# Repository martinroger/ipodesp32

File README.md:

# iPodESP32 : an iPod emulator for 2nd gen Minis

## CAVEAT
> [!WARNING]
> At the time of this commit, it has become apparent that the all CP2102 chips are not born equal. The hack consisting of spoofing a PL2303HX by overwriting the PID and VID on a CP2102 **only works on older versions**. I haven't yet managed to get it to work on CP2102N or CP2102-GM transceivers. Additionally, I haven't managed to get this hack to work on CP2104 or FTDI232R transceivers. For the time being, I would recommend holding off from ordering boards based on the designs in PCB unless you are certain you can source pre-2018 CP2102 chips.
> Work is happening on finding a solution, as the PL2303TA that would be the ideal candidate is hard to find in stock too.
> 
> **I may have found a practical solution by getting an ESP32S3 to spoof being a PL2303HX. Release v1.0.0 will introduce that solution !**

## Summary (TL;DR)

Second generation Minis (R56, R57, R58...) did not come with Bluetooth music streaming unless the Visual Boost or Mini Connected navigation option was selected (which wasn't hugely popular). 
Some of the later Minis (usually called LCI, or facelift Mini) started shipping with iPod support in the form of an USB receptacle, a 3.5mm AUX input and a special "Y-Cable". 

This repository is an attempt at bridging that gap with an ESP32 and a bag of tricks to provide **BT music streaming, retaining track data on the display and radio/steering wheel playback controls.**

## What is needed

Aside from a [Mini with a compatible radio head unit](https://github.com/martinroger/ipodesp32/wiki/How-to-identify-compatible-Minis) : 

- For the [full-DIY build](https://github.com/martinroger/ipodesp32/wiki/DIY-DAC%E2%80%90based-solution-(UDA1334A)) :
  - An ESP32 (not S3!) that has Bluetooth Classic or EDR support
  - A DAC (UDA1334 or PCM5102) breakout board
  - A CP2102 ~~or CP2104~~ breakout board with exposed DCD pin (no CP2102N or CP2102GM)
  - Jumper wires
  - Possibly some smaller hardware (resistors, capacitors) and a soldering iron

- For the Sandwich Carrier Board build, [follow this article](https://github.com/martinroger/ipodesp32/wiki/Sandwich-Carrier-Board-build)
- For the ESP32 AudioKit Top Hat build, [follow this other article](https://github.com/martinroger/ipodesp32/wiki/AudioKit-and-Haut%E2%80%90de%E2%80%90Forme-board)
- For the fancy ones out there wanting a small ESP32 A1S Mini, [it's here](https://github.com/martinroger/ipodesp32/wiki/ESP32%E2%80%90A1S%E2%80%90Mini-build)
- For the fancy but alternative-minded ones who also want an All-In-One, [it's there](https://github.com/martinroger/ipodesp32/wiki/ESP32%E2%80%90AiO-build)

## Alternative solutions

Over the year, some companies (mostly in China) have developped similar devices, such as the ones sold by **[Bovee](https://a.co/d/5lkZTkV)** or **[Gitank](https://thegitank.com/products/gitank-bluetooth-5-0-aptx-hd-adapter-with-y-cable-for-bmw-and-mini-cooper-usb-aux-ipod-iphone-music-interface-300b)**. The general principle is the same : a BT speaker is running an A2DP profile, while sufficient iPod-like communication is performed with the Mini to make it think there is an actual iPod connected.

I have had a very mixed bag of results with those, and it appeared to be even worse when using an Android phone, as the Playback/Synchronisation/Metadata seemed to be mostly reserved to iPhone users. Playback controls were also hit-and-miss.

## The iPodESP32 solution

Beyond the lame name, the solution proposed here does the following :

- Emulates an iPod Classic 5 - the U2 edition to be precise
- Passes song metadata from the phone/tablet (**Android or iOs**... or even others ?) regardless of what is playing the songs (Spotify remains the most tested to this date)
- Enables direct playback control from the radio interface, including steering wheel controls if present
- Auto-reconnects on ignition on, auto-pauses on ignition off
- Auto-pause and passes to whichever handsfree solution is present in case of phone call
- Provides many different interfaces for debug logging... because surely I didn't catch all them bugs
- Does not require any permanent modification of the car

## External (essential) libraries used

Respect where is due to the underlying libraries needed for this to work : 
- [AudioTools](https://github.com/pschatzmann/arduino-audio-tools)
- [ESP32-A2DP library](https://github.com/pschatzmann/ESP32-A2DP)
- [Arduino Audio Driver](https://github.com/pschatzmann/arduino-audio-driver)

## How to use it, and some tips

Although it should be pretty straightforward at this stage, to use this, you need to connect the USB with the modified VID/PID to the USB receptacle of the car, and the audio jack to the AUX input (with a male-male stereo cable, for example).

In its default configuration, the controller will wait for an established BT connection to a phone before it starts signalling to the vehicle that it is available. This is only necessary the first time a phone is connected to it, in other cases the controller will try to auto-reconnect.

Once the controller has established connection with the phone, it starts the handshake process with the head unit, and if all is good the Aux and USB options in the "Mode" source selector of the head unit are replaced by an "iPod" option. This normally takes a few seconds if the controller was just connected, so re-check after 10s if the iPod option is not available.
If it still doesn't come up, in some occasions it is necessary to disconnect the USB cable, wait 5-10 seconds and reconnect it and wait for the BT pairing to go through (check your phone!).

The Mini will try to automatically start playback once the iPod option is selected. Depending on your phone configuration, it may automatically open your favourite music player and start playing. In some cases it might be necessary to manually open a music player for things to get started. At this stage the display should update with the track info.

When you leave the car, the USB gets shut down after about 2 minutes (no risks of draining the battery) and normally the Mini negotiates a playback pause as the ignition is turned off...

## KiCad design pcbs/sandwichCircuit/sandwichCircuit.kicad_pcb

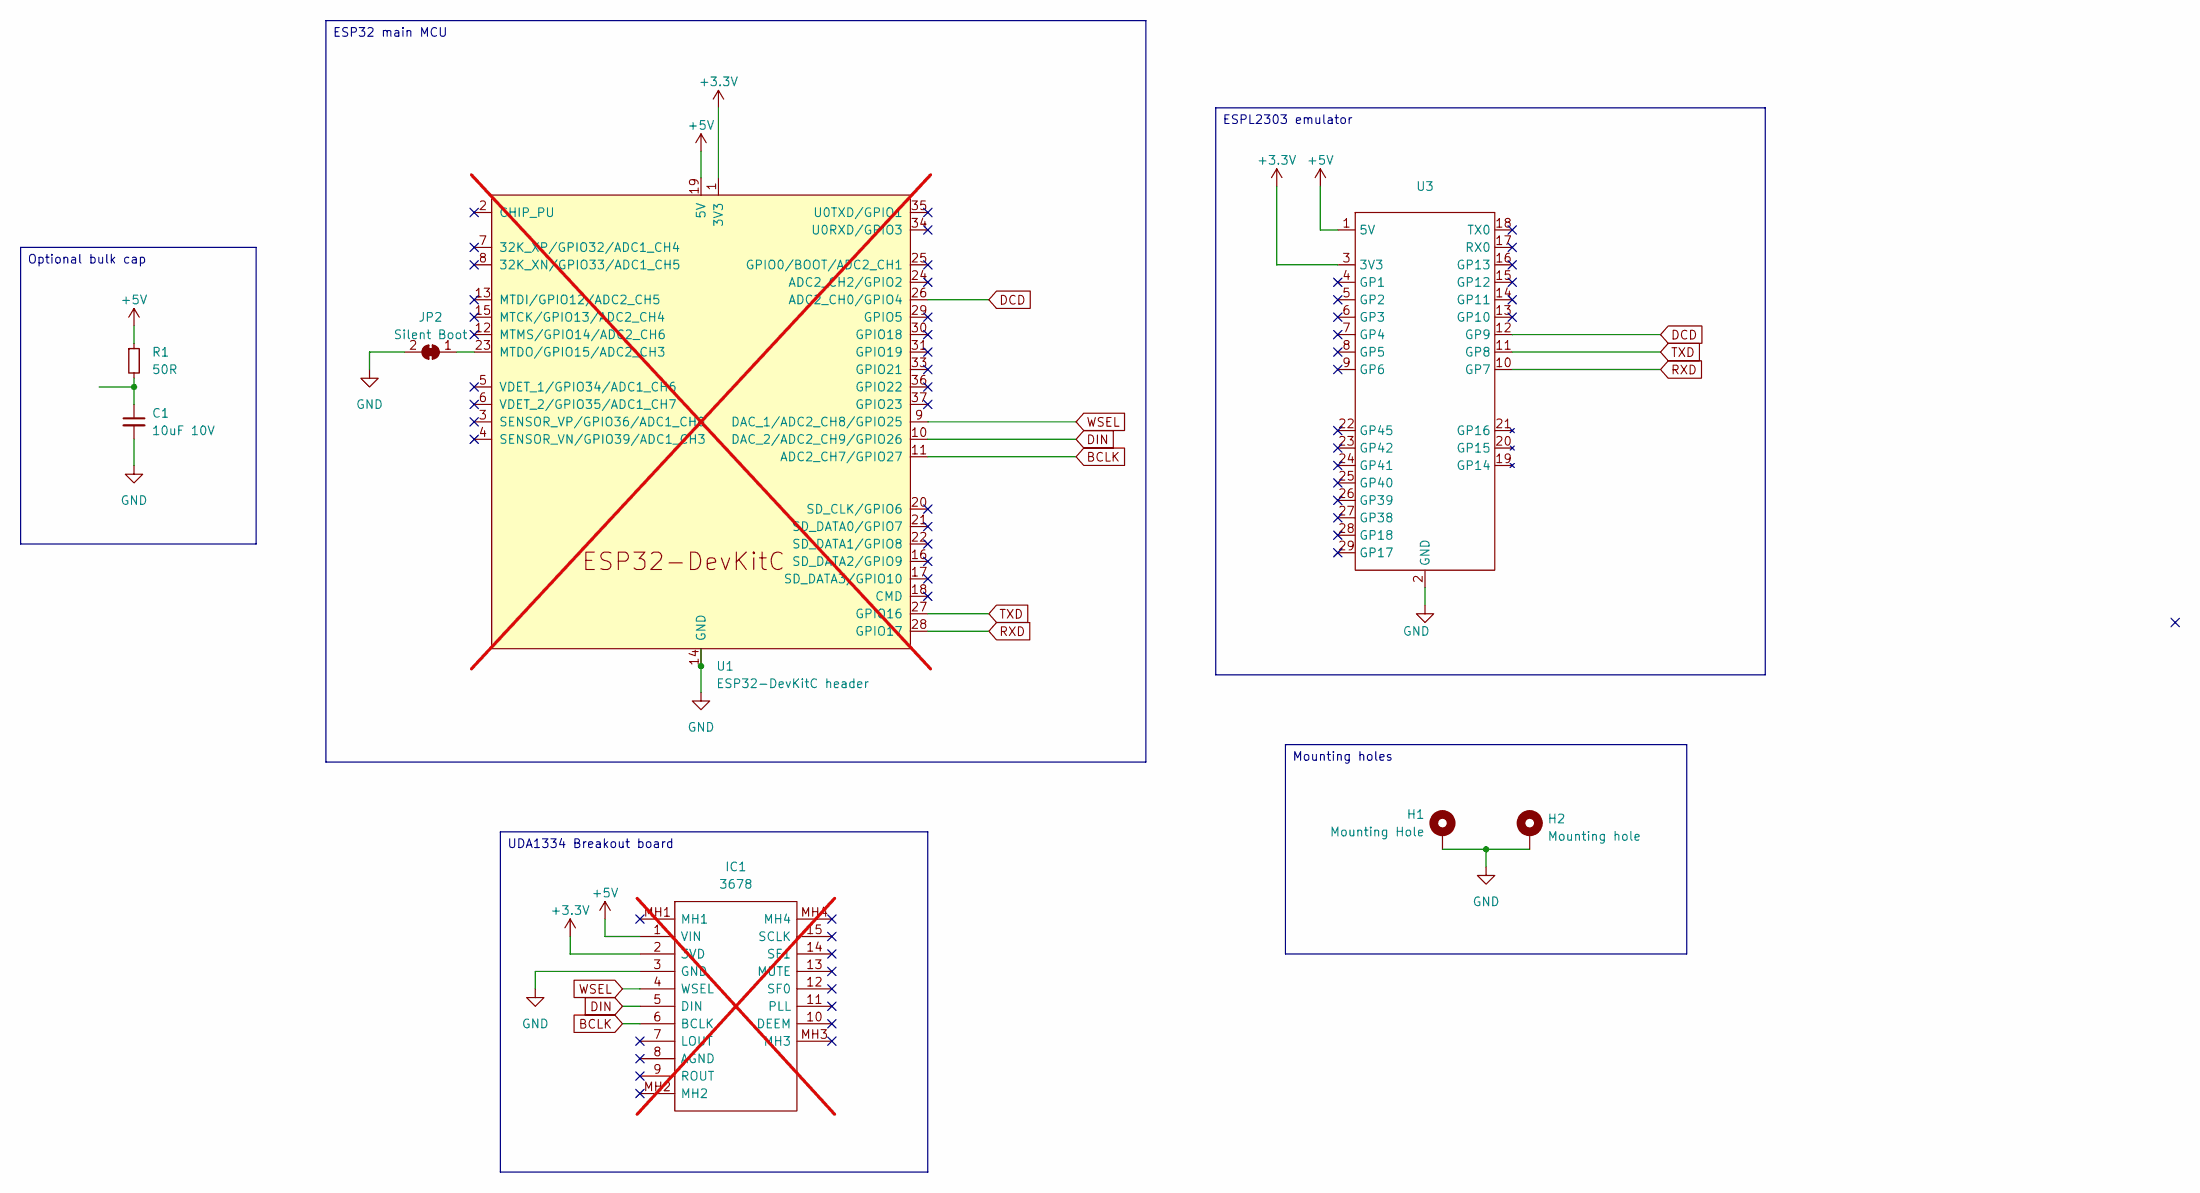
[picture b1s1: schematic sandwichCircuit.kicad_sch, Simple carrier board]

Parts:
C1: 10uF 10V; C_Radial_D5.0mm_H7.0mm_P2.00mm
H1: Mounting Hole; MountingHole_3.2mm_M3_Pad_TopBottom
H2: Mounting hole; MountingHole_3.2mm_M3_Pad_TopBottom
IC1: 3678; Manufacturer_Part_Number 3678; Mouser Part Number 485-3678; not fitted
JP2: Silent Boot; SolderJumper-2_P1.3mm_Bridged_RoundedPad1.0x1.5mm
R1: 50R; R_Axial_DIN0207_L6.3mm_D2.5mm_P10.16mm_Horizontal
U1: ESP32-DevKitC header; ESP32-DevKitC; not fitted
U3: Waveshare ESP32 S3 Zero THT

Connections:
+3.3V: IC1.2 (3VD), U1.1 (3V3), U3.3 (3V3)
+5V: IC1.1 (VIN), R1.1, U1.19 (5V), U3.1 (5V)
BCLK: IC1.6 (BCLK), U1.11 (ADC2_CH7/GPIO27)
DCD: U1.26 (ADC2_CH0/GPIO4), U3.12 (GP9)
DIN: IC1.5 (DIN), U1.10 (DAC_2/ADC2_CH9/GPIO26)
GND: C1.2, H1.1, H2.1, IC1.3 (GND), JP2.2 (B), U1.14 (GND), U1.32 (GND), U1.38 (GND), U3.2 (GND)
unnamed: C1.1, R1.2
unnamed: JP2.1 (A), U1.23 (MTDO/GPIO15/ADC2_CH3)
RXD: U1.28 (GPIO17), U3.10 (GP7)
TXD: U1.27 (GPIO16), U3.11 (GP8)
WSEL: IC1.4 (WSEL), U1.9 (DAC_1/ADC2_CH8/GPIO25)

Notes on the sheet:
ESP32 main MCU
Mounting holes
Optional bulk cap
UDA1334 Breakout board
ESPL2303 emulator

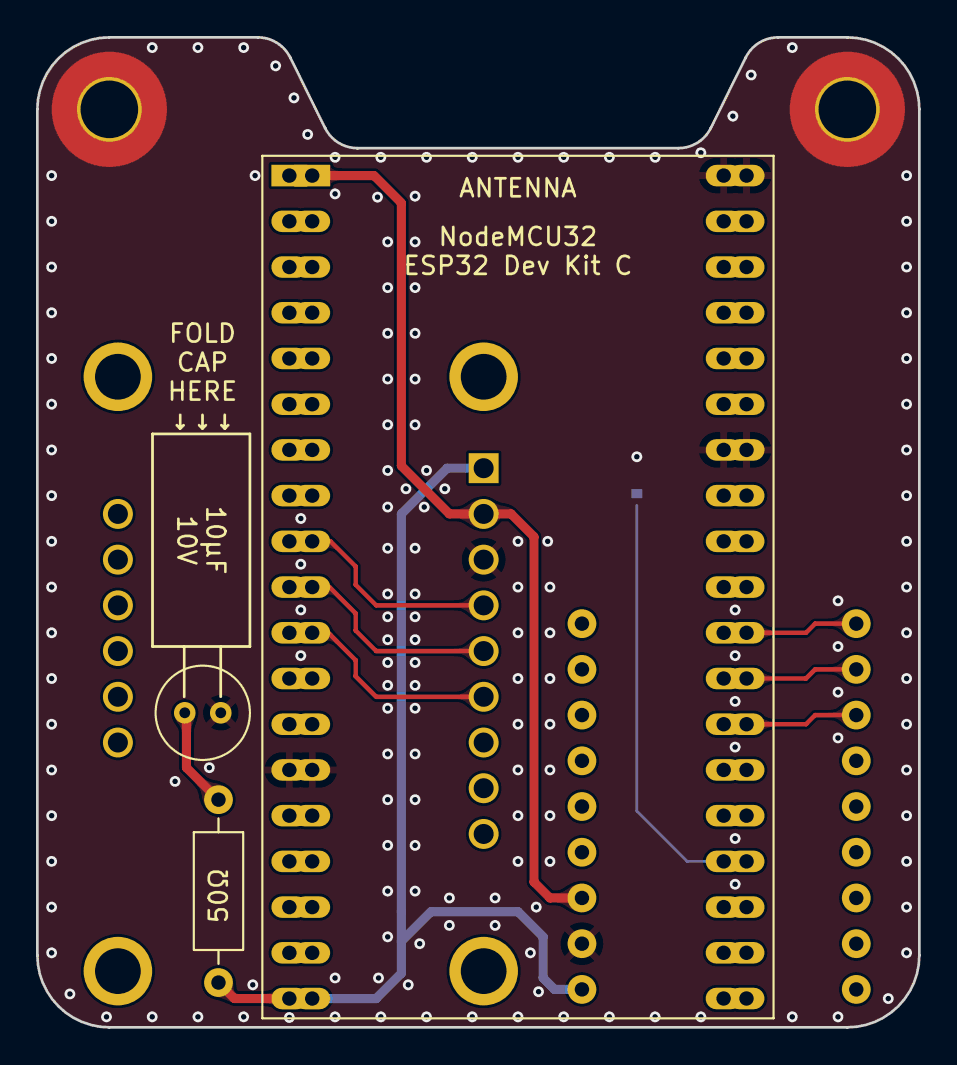
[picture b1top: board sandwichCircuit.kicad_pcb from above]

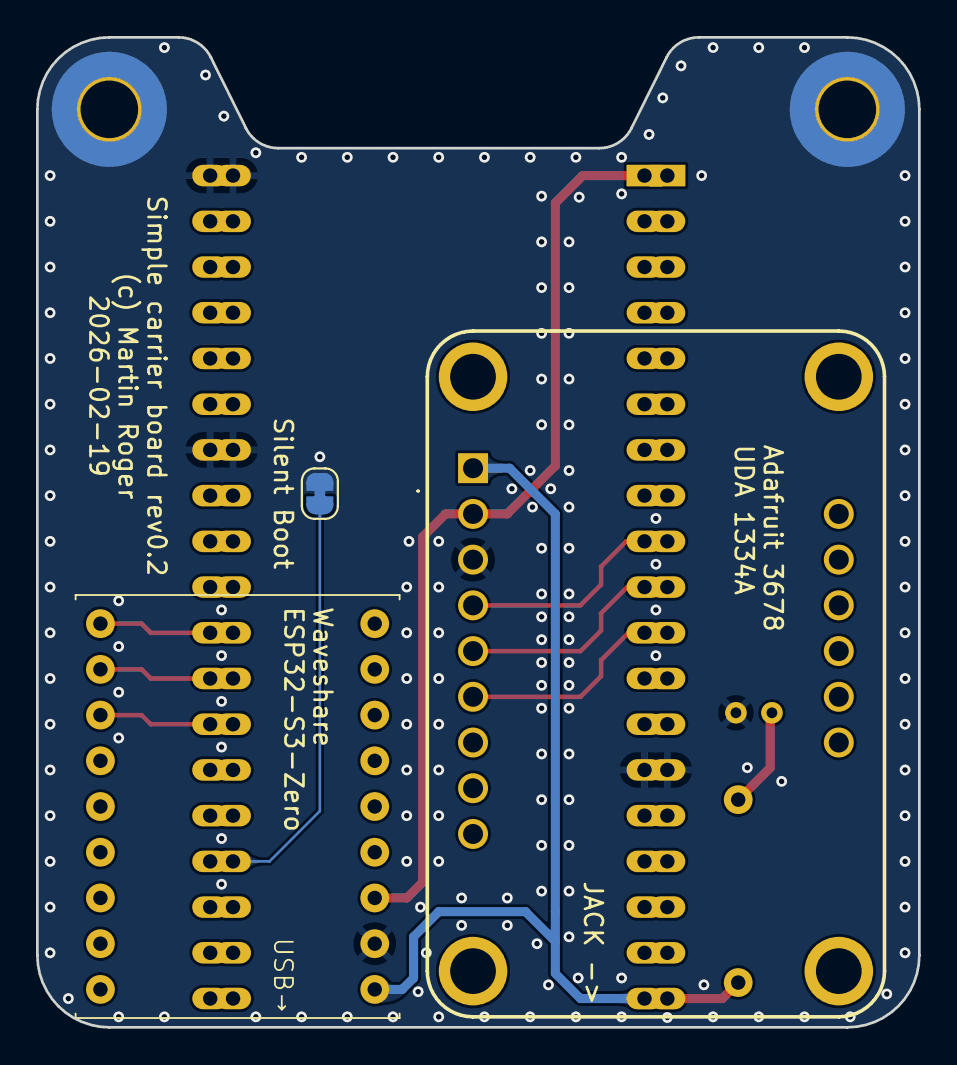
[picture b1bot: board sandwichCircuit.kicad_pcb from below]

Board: 2 copper layers, 49.0 x 55.0 mm, 8 parts (3 on the bottom side), 11 nets.

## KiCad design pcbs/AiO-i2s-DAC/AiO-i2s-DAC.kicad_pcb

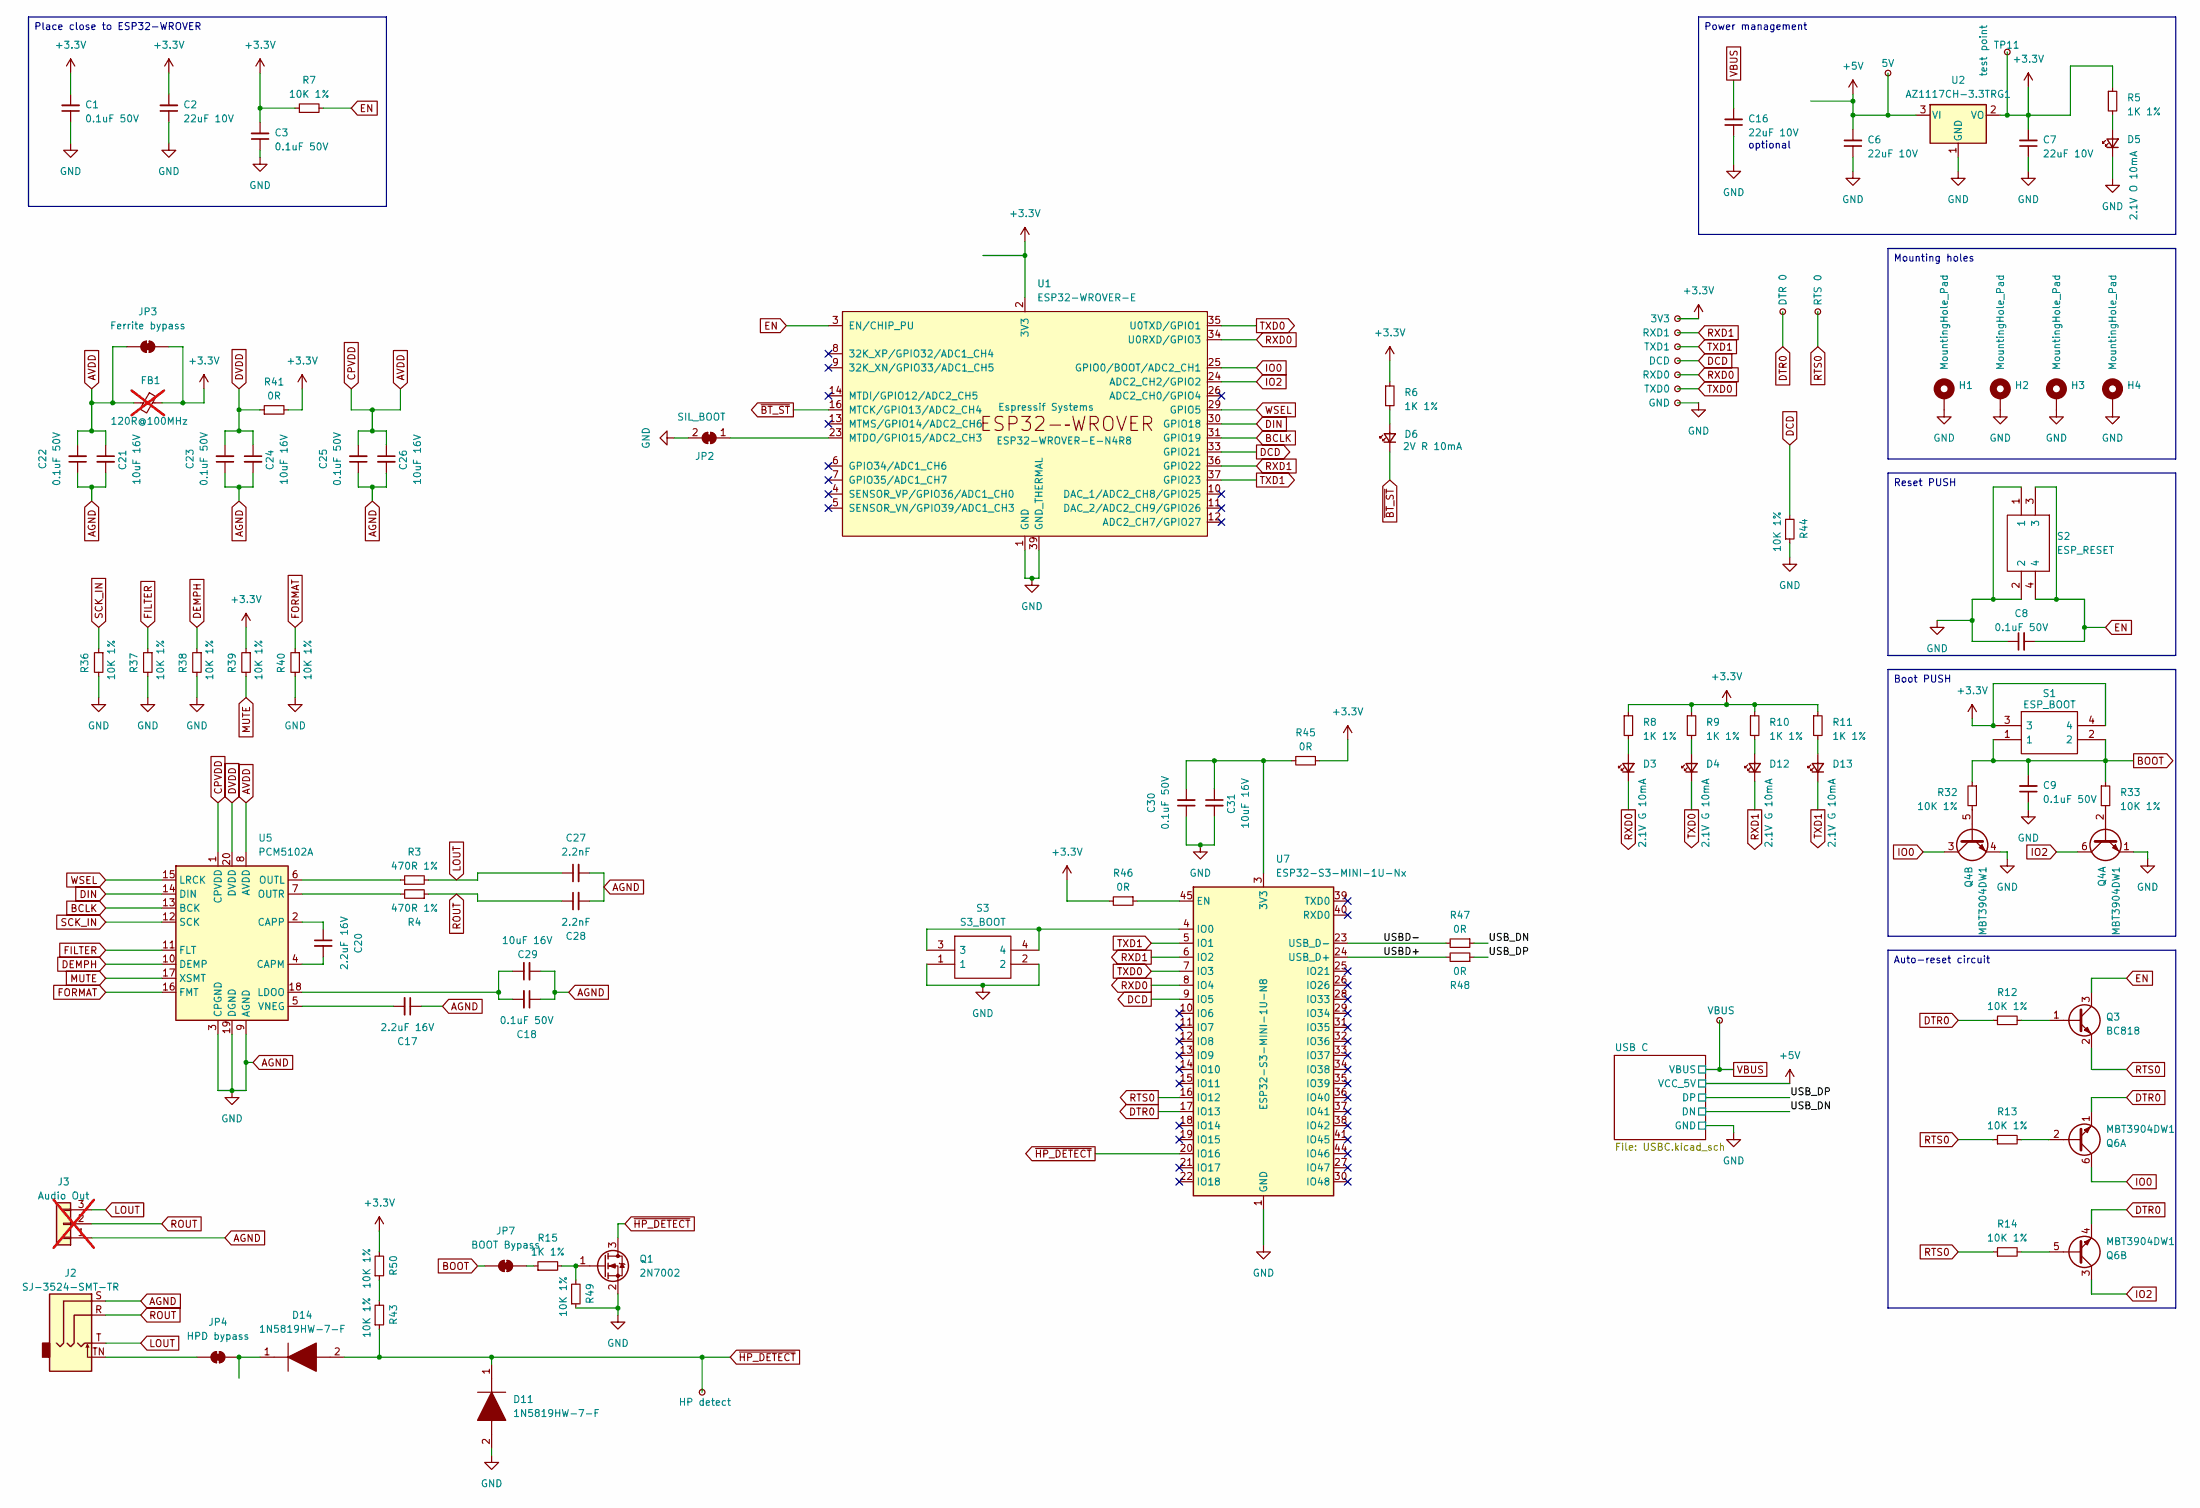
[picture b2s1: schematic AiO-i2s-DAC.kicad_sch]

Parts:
C1, C3, C8, C9, C18, C22, C23, C25, C30: 0.1uF 50V; C_0603_1608Metric; Manufacturer_Part_Number CL10B104KB8NNNC; LCSC C14663
C2, C6, C7, C16: 22uF 10V; C_0805_2012Metric; Manufacturer_Part_Number CC0805MKX5R6BB226; LCSC C45783
C17, C20: 2.2uF 16V; C_0603_1608Metric; Manufacturer_Part_Number CL10A225KO8NNNC; LCSC C23630
C21, C24, C26, C29, C31: 10uF 16V; C_0805_2012Metric; Manufacturer_Part_Number CL21A106KOQNNNG; LCSC C15850
C27, C28: 2.2nF; C_0603_1608Metric; Manufacturer_Part_Number CC0603KRX7R9BB222; LCSC C1604
D3, D4, D12, D13: 2.1V G 10mA; LED_0603_1608Metric; Manufacturer_Part_Number LTST-C190GKT; LCSC C2286
D5: 2.1V O 10mA; LED_0603_1608Metric; Manufacturer_Part_Number LTST-C190AKT; LCSC C2286
D6: 2V R 10mA; LED_0603_1608Metric; Manufacturer_Part_Number LTST-C190EKT; LCSC C2286
D11, D14: 1N5819HW-7-F; SOD3716X145N; Manufacturer_Part_Number 1N5819HW-7-F; LCSC C82544
FB1: 120R@100MHz; L_0603_1608Metric; Manufacturer_Part_Number MAF1608GAD601CT000; LCSC C2661571; not fitted
H1, H2, H3, H4: MountingHole_Pad; MountingHole_3.2mm_M3_Pad_TopBottom
J2: SJ-3524-SMT-TR; Jack_3.5mm_CUI_SJ-3524-SMT_Horizontal; Manufacturer_Part_Number PJ-328-4A; LCSC C2910529
J3: Audio Out; PinHeader_1x03_P2.54mm_Vertical; not fitted
JP2: SIL_BOOT; SolderJumper-2_P1.3mm_Bridged_RoundedPad1.0x1.5mm
JP3: Ferrite bypass; SolderJumper-2_P1.3mm_Open_RoundedPad1.0x1.5mm
JP4: HPD bypass; SolderJumper-2_P1.3mm_Bridged_RoundedPad1.0x1.5mm
JP7: BOOT Bypass; SolderJumper-2_P1.3mm_Bridged_RoundedPad1.0x1.5mm
Q1: 2N7002; SOT-23; Manufacturer_Part_Number 2N7002-TP; LCSC C78712
Q3: BC818; SOT-23; Manufacturer_Part_Number BC818-40LT1G; LCSC C154797
Q4, Q6: MBT3904DW1; SOT-363_SC-70-6; Manufacturer_Part_Number MBT3904DW1T1G; LCSC C131781
R3, R4: 470R 1%; R_0603_1608Metric; Manufacturer_Part_Number RC0603FR-07470RL; LCSC C114669
R5, R6, R8, R9, R10, R11, R15: 1K 1%; R_0603_1608Metric; Manufacturer_Part_Number RC0603FR-071KL; LCSC C21190
R7, R12, R13, R14, R32, R33, R36, R37, R38, R39, R40, R43, R44, R49, R50: 10K 1%; R_0603_1608Metric; Manufacturer_Part_Number CR0603-FX-1002ELF; LCSC C25804
R41, R45, R46, R47, R48: 0R; R_0603_1608Metric; Manufacturer_Part_Number RMCF0603ZT0R00; LCSC C21189
S1: ESP_BOOT; TL3305BF260QG; Manufacturer_Part_Number TS4550TP; LCSC C412373
S2: ESP_RESET; TL3305BF260QG; Manufacturer_Part_Number TS4550TP; LCSC C412373
S3: S3_BOOT; TL3305BF260QG; Manufacturer_Part_Number TS4550TP; LCSC C412373
TP1: 3V3; TestPoint_Pad_D2.0mm
TP2: RXD1; TestPoint_Pad_D2.0mm
TP3: TXD1; TestPoint_Pad_D2.0mm
TP4: DCD; TestPoint_Pad_D2.0mm
TP5: GND; TestPoint_Pad_D2.0mm
TP6: RXD0; TestPoint_Pad_D2.0mm
TP7: TXD0; TestPoint_Pad_D2.0mm
TP8: VBUS; TestPoint_Pad_D1.0mm
TP9: DTR 0; TestPoint_Pad_D2.0mm
TP10: RTS 0; TestPoint_Pad_D2.0mm
TP11: 3V3; TestPoint_Pad_D1.0mm
TP12: 5V; TestPoint_Pad_D1.0mm
TP13: HP detect; TestPoint_Pad_D2.0mm
U1: ESP32-WROVER-E; ESP32-WROVER-E_ThermalVias; Manufacturer_Part_Number ESP32-WROVER-E-N4R8; LCSC C967023
U2: AZ1117CH-3.3TRG1; SOT-223-3_TabPin2; Manufacturer_Part_Number AZ1117CH-3.3TRG1; LCSC C6186
U5: PCM5102A; TSSOP-20_4.4x6.5mm_P0.65mm; Manufacturer_Part_Number PCM5102APWR; LCSC C107671
U7: ESP32-S3-MINI-1U-Nx; ESP32-S3-MINI-1U; Manufacturer_Part_Number ESP32-S3-MINI-1U-N8; LCSC C2980299

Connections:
+3.3V: C1.2, C2.2, C3.2, C7.2, FB1.1, JP3.2 (B), R5.1, R6.1, R7.1, R8.1, R9.1, R10.1, R11.1, R39.1, R41.2, R45.1, R46.2, R50.2, S1.3, S1.4, TP1.1, TP11.1, U1.2 (3V3), U2.2 (VO)
+5V: C6.2, TP12.1, U2.3 (VI); also elsewhere on the board
/USBD+: R48.2, U7.24 (USB_D+)
/USBD-: R47.2, U7.23 (USB_D-)
/USB_DN: R47.1; also elsewhere on the board
/USB_DP: R48.1; also elsewhere on the board
AGND: C1.1, C2.1, C3.1, C6.1, C7.1, C8.1, C9.1, C16.1, C17.1, C18.1, C21.2, C22.1, C23.1, C24.2, C25.1, C26.2, C27.2, C28.2, C29.2, C30.1, C31.2, D5.1 (K), D11.2, H1.1, H2.1, H3.1, H4.1, J2.S, JP2.2 (B), Q1.2 (S), Q4.1 (E1), Q4.4 (E2), R36.2, R37.2, R38.2, R40.2, R44.1, R49.1, S2.1, S2.2, S3.1, S3.2, TP5.1, U1.1 (GND), U1.15 (GND), U1.38 (GND), U1.39 (GND_THERMAL), U2.1 (GND), U5.3 (CPGND), U5.9 (AGND), U5.19 (DGND), U7.1 (GND), U7.2 (GND), U7.42 (GND), U7.43 (GND), U7.46 (GND), U7.47 (GND), U7.48 (GND), U7.49 (GND), U7.50 (GND), U7.51 (GND), U7.52 (GND), U7.53 (GND), U7.54 (GND), U7.55 (GND), U7.56 (GND), U7.57 (GND), U7.58 (GND), U7.59 (GND), U7.60 (GND), U7.61 (GND), U7.62 (GND), U7.63 (GND), U7.64 (GND), U7.65 (GND); also elsewhere on the board
AVDD: C21.1, C22.2, C25.2, C26.1, FB1.2, JP3.1 (A), U5.1 (CPVDD), U5.8 (AVDD)
BCLK: U1.31 (GPIO19), U5.13 (BCK)
BOOT: C9.2, JP7.1 (A), R32.1, R33.1, S1.1, S1.2
DCD: R44.2, TP4.1, U1.33 (GPIO21), U7.9 (IO5)
DEMPH: R38.1, U5.10 (DEMP)
DIN: U1.30 (GPIO18), U5.14 (DIN)
DTR0: Q6.1 (E1), Q6.4 (E2), R12.1, TP9.1, U7.17 (IO13)
DVDD: C23.2, C24.1, R41.1, U5.20 (DVDD)
EN: C8.2, Q3.3 (C), R7.2, S2.3, S2.4, U1.3 (EN/CHIP_PU)
FILTER: R37.1, U5.11 (FLT)
FORMAT: R40.1, U5.16 (FMT)
IO0: Q4.3 (C2), Q6.6 (C1), U1.25 (GPIO0/BOOT/ADC2_CH1)
IO2: Q4.6 (C1), Q6.3 (C2), U1.24 (ADC2_CH2/GPIO2)
LOUT: C27.1, J2.T, J3.3, R3.2
MUTE: R39.2, U5.17 (XSMT)
unnamed: D3.2 (A), R8.2
unnamed: D4.2 (A), R9.2
unnamed: D5.2 (A), R5.2
unnamed: D6.2 (A), R6.2
unnamed: D12.2 (A), R10.2
unnamed: D13.2 (A), R11.2
unnamed: JP2.1 (A), U1.23 (MTDO/GPIO15/ADC2_CH3)
unnamed: J2.TN, JP4.1 (A)
unnamed: D14.1, JP4.2 (B)
unnamed: JP7.2 (B), R15.1
unnamed: Q1.1 (G), R15.2, R49.2
unnamed: Q3.1 (B), R12.2
unnamed: Q4.2 (B1), R33.2
unnamed: Q4.5 (B2), R32.2
unnamed: Q6.2 (B1), R13.2
unnamed: Q6.5 (B2), R14.2
unnamed: R43.2, R50.1
unnamed: C20.2, U5.4 (CAPM)
unnamed: C20.1, U5.2 (CAPP)
unnamed: C18.2, C29.1, U5.18 (LDOO)
unnamed: R3.1, U5.6 (OUTL)
unnamed: R4.2, U5.7 (OUTR)
unnamed: C17.2, U5.5 (VNEG)
unnamed: C30.2, C31.1, R45.2, U7.3 (3V3)
unnamed: R46.1, U7.45 (EN)
unnamed: S3.3, S3.4, U7.4 (IO0)
ROUT: C28.1, J2.R, J3.2, R4.1
RTS0: Q3.2 (E), R13.1, R14.1, TP10.1, U7.16 (IO12)
RXD0: D3.1 (K), TP6.1, U1.34 (U0RXD/GPIO3), U7.8 (IO4)
RXD1: D12.1 (K), TP2.1, U1.36 (GPIO22), U7.6 (IO2)
SCK_IN: R36.1, U5.12 (SCK)
TXD0: D4.1 (K), TP7.1, U1.35 (U0TXD/GPIO1), U7.7 (IO3)
TXD1: D13.1 (K), TP3.1, U1.37 (GPIO23), U7.5 (IO1)
VBUS: C16.2, TP8.1; also elsewhere on the board
WSEL: U1.29 (GPIO5), U5.15 (LRCK)
~BT_ST: D6.1 (K), U1.16 (MTCK/GPIO13/ADC2_CH4)
~HP_DETECT: D11.1, D14.2, Q1.3 (D), R43.1, TP13.1, U7.20 (IO16)

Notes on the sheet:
optional
Boot PUSH
Reset PUSH
Mounting holes
Auto-reset circuit
Place close to ESP32-WROVER
Power management

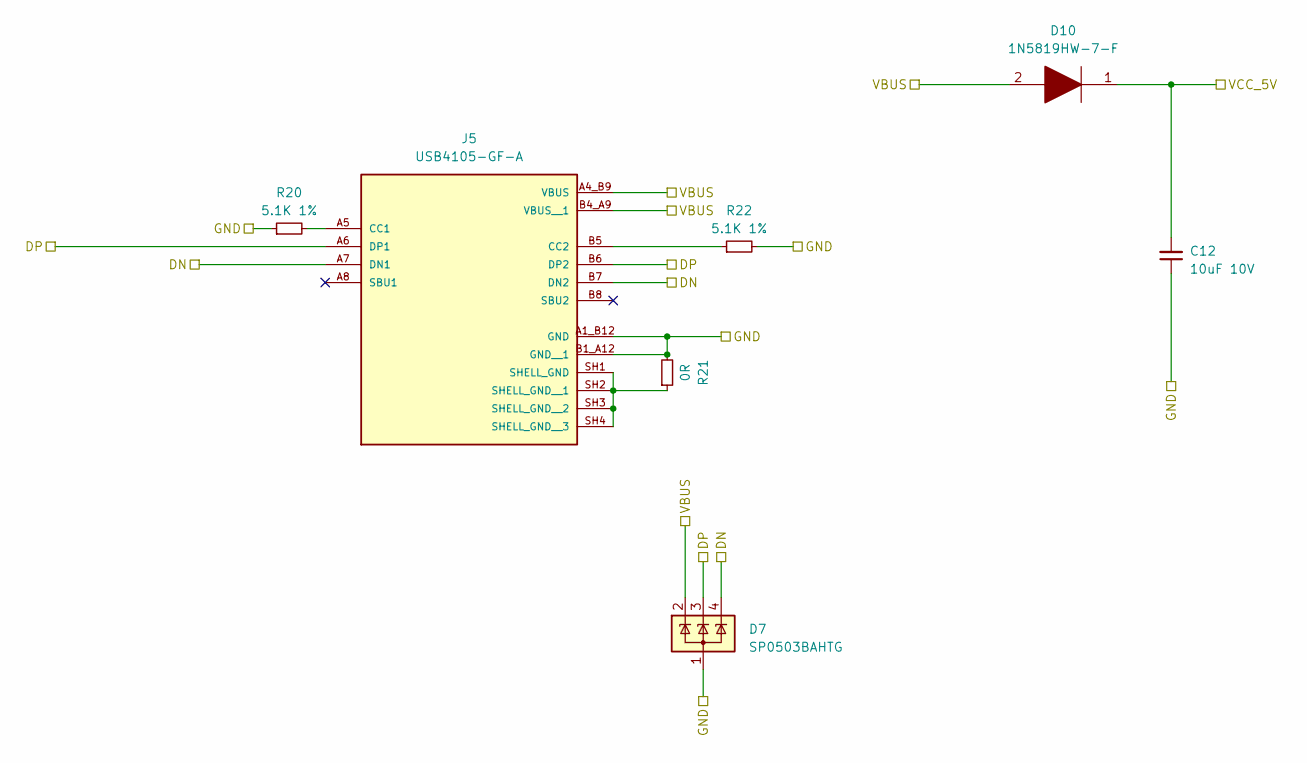
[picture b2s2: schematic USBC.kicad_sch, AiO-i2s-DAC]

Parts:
C12: 10uF 10V; C_0603_1608Metric; Manufacturer_Part_Number CL10A106KP8NNNC; LCSC C19702
D7: SP0503BAHTG; SOT-143; Manufacturer_Part_Number SP0503BAHTG; LCSC C41364459
D10: 1N5819HW-7-F; SOD3716X145N; Manufacturer_Part_Number 1N5819HW-7-F; LCSC C82544
J5: USB4105-GF-A; GCT_USB4105-GF-A; PARTREV B4; LCSC C3020560
R20, R22: 5.1K 1%; R_0603_1608Metric; Manufacturer_Part_Number RC0603FR-075K1L; LCSC C23186
R21: 0R; R_0603_1608Metric; Manufacturer_Part_Number RMCF0603ZT0R00; LCSC C21189

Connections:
+5V: C12.2, D10.1; also elsewhere on the board
/USB_DN: D7.4 (K), J5.A7 (DN1), J5.B7 (DN2); also elsewhere on the board
/USB_DP: D7.3 (K), J5.A6 (DP1), J5.B6 (DP2); also elsewhere on the board
AGND: C12.1, D7.1 (A), J5.A1_B12 (GND), J5.B1_A12 (GND__1), R20.1, R21.2, R22.2; also elsewhere on the board
unnamed: J5.A5 (CC1), R20.2
unnamed: J5.B5 (CC2), R22.1
unnamed: J5.SH1 (SHELL_GND), J5.SH2 (SHELL_GND__1), J5.SH3 (SHELL_GND__2), J5.SH4 (SHELL_GND__3), R21.1
VBUS: D7.2 (K), D10.2, J5.A4_B9 (VBUS), J5.B4_A9 (VBUS__1); also elsewhere on the board

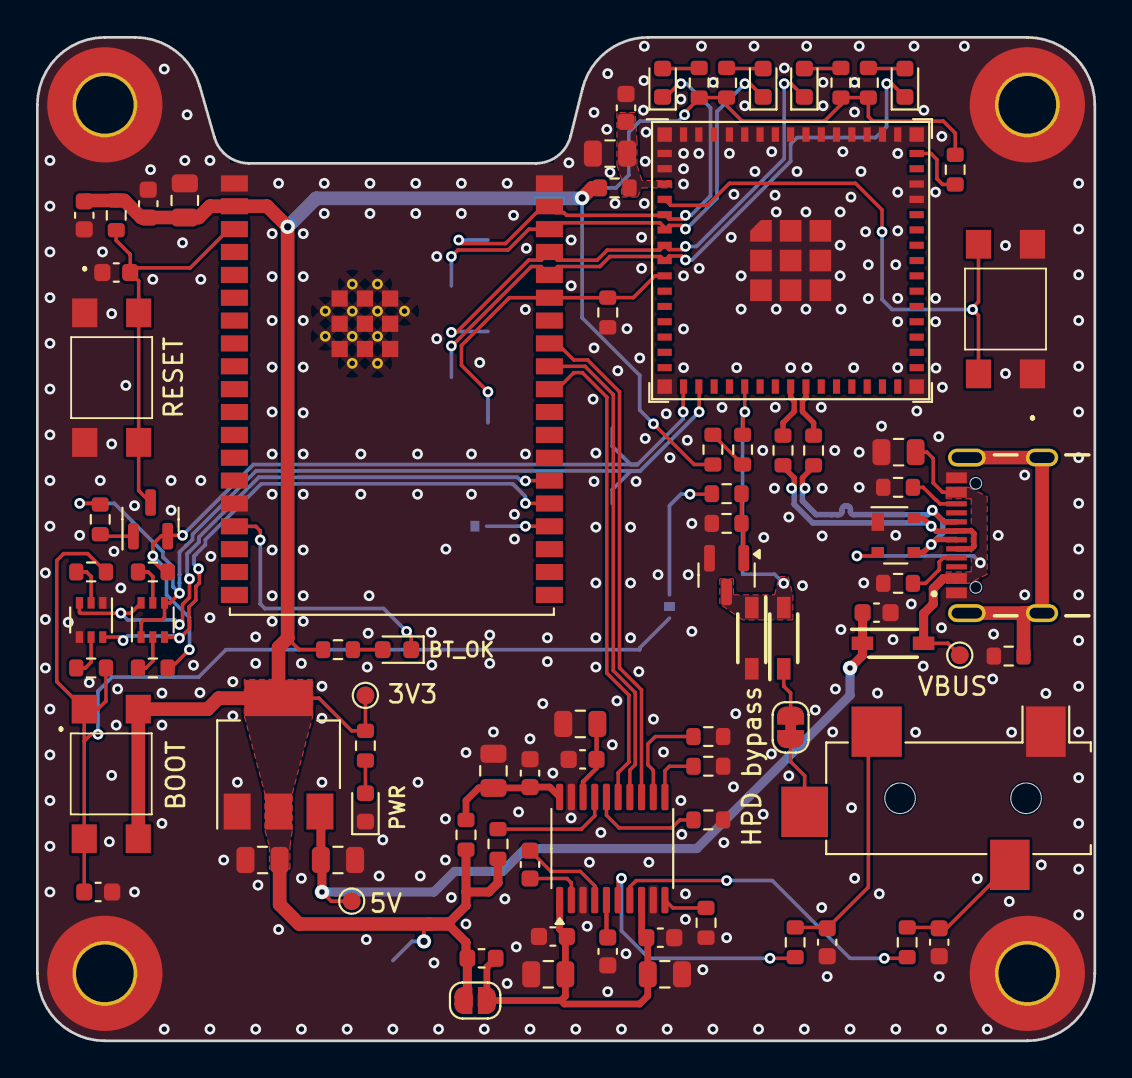
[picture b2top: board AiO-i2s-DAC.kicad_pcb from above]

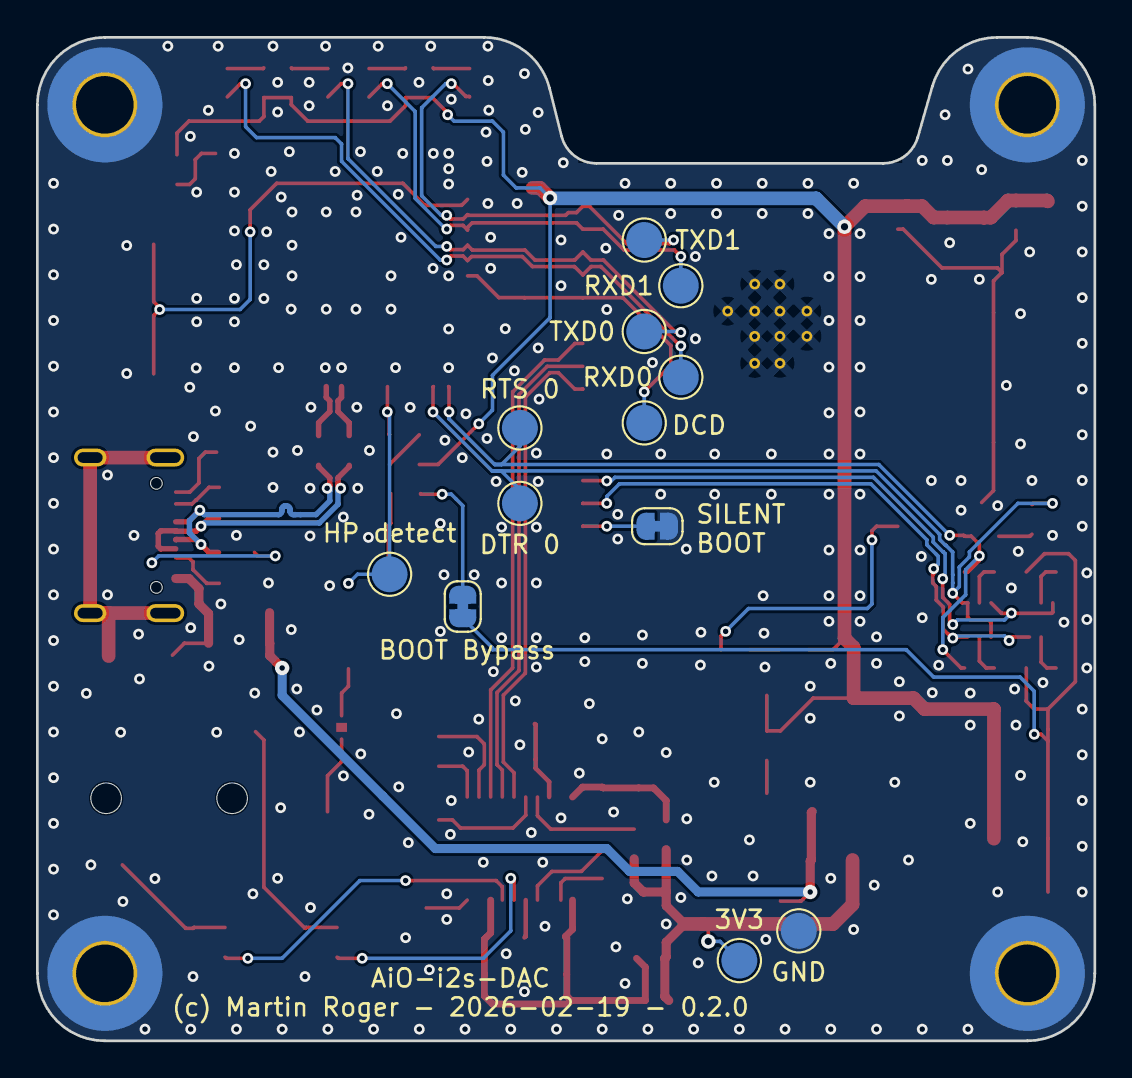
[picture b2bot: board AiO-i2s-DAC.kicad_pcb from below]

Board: 2 copper layers, 58.8 x 55.7 mm, 100 parts (12 on the bottom side), 62 nets.
